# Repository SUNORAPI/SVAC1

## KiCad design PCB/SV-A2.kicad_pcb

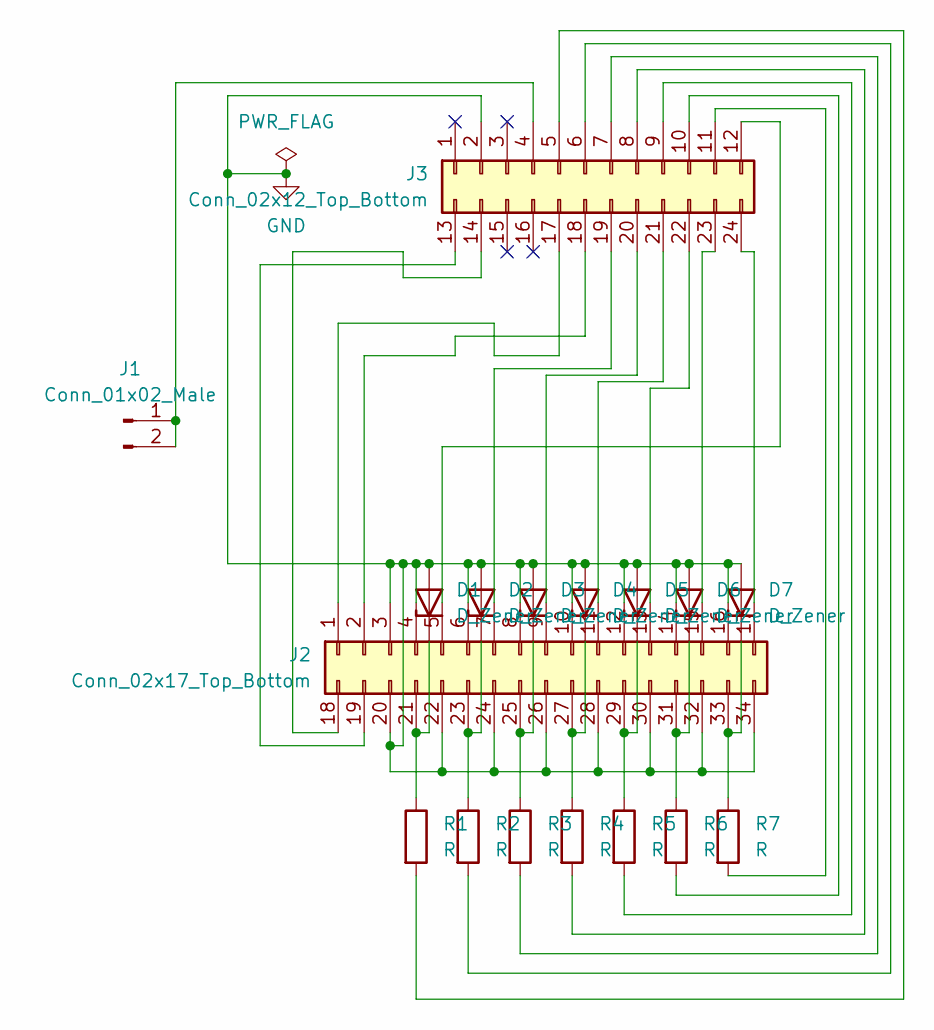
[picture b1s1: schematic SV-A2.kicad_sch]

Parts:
D1, D2, D3, D4, D5, D6, D7: D_Zener; BZX55C5V1
J1: Conn_01x02_Male; B02B-XASK-1N
J2: Conn_02x17_Top_Bottom; B34B-XASDSS-N
J3: Conn_02x12_Top_Bottom; ProMicro_Connector
R1, R2, R3, R4, R5, R6, R7: R; CF25J68RB

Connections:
GND: D1.2 (A), D2.2 (A), D3.2 (A), D4.2 (A), D5.2 (A), D6.2 (A), D7.2 (A), J2.3, J2.4, J2.6, J2.8, J2.10, J2.12, J2.14, J2.16, J2.20, J2.22, J2.24, J2.26, J2.28, J2.30, J2.32, J2.34, J3.2
unnamed: D1.1 (K), J2.21, R1.1
unnamed: D2.1 (K), J2.23, R2.1
unnamed: D3.1 (K), J2.25, R3.1
unnamed: D4.1 (K), J2.27, R4.1
unnamed: D5.1 (K), J2.29, R5.1
unnamed: D6.1 (K), J2.31, R6.1
unnamed: D7.1 (K), J2.33, R7.1
unnamed: J1.1, J1.2, J3.4
unnamed: J2.1, J3.17
unnamed: J2.5, J3.12
unnamed: J2.7, J3.19
unnamed: J2.9, J3.20
unnamed: J2.11, J3.21
unnamed: J2.13, J3.22
unnamed: J2.15, J3.23
unnamed: J2.17, J3.24
unnamed: J2.19, J3.13
unnamed: J3.5, R1.2
unnamed: J3.6, R2.2
unnamed: J3.7, R3.2
unnamed: J3.8, R4.2
unnamed: J3.9, R5.2
unnamed: J3.10, R6.2
unnamed: J3.11, R7.2
unnamed: J2.18, J3.14
unnamed: J2.2, J3.18

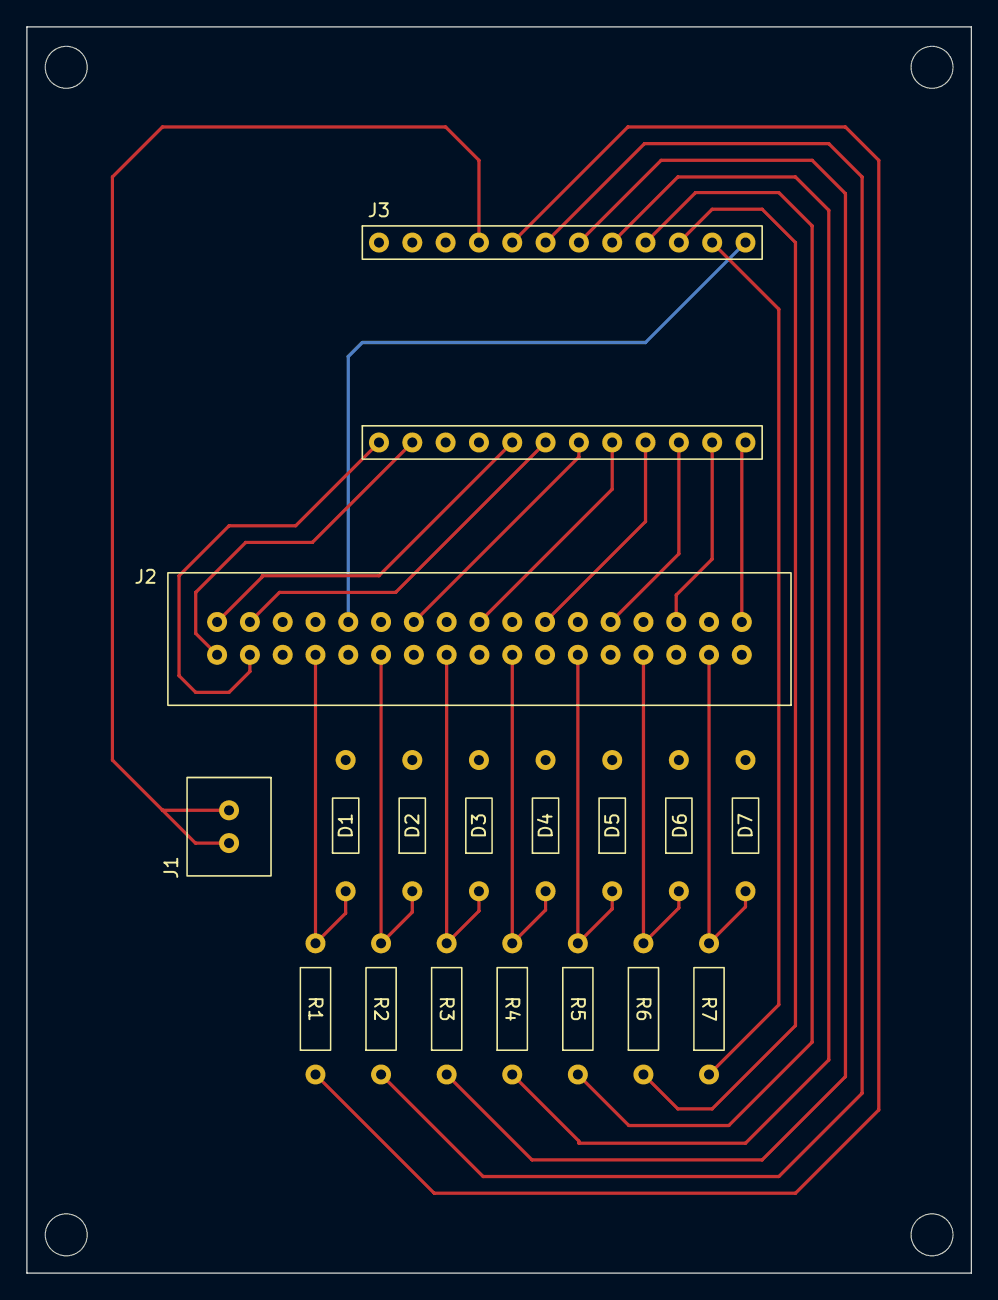
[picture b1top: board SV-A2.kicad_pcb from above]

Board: 2 copper layers, 72.0 x 95.0 mm, 17 parts (0 on the bottom side), 27 nets.

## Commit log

2024-12-15 InitialCommit
